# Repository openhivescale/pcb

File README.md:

PCB schemas and boards, eagle format (7.5)

mainboard is... the main board, with MCU including wifi, power, motor driver etc...

On this mainboard can be plugged ONE of the shield : 

- SFM10R1 : sifgox (Europe)
- RN2483A : LoraWan
- SIM800L : GSM 2G
- SIM7000E : GSM 4G Nb-IoT

- template : base for a future new shield

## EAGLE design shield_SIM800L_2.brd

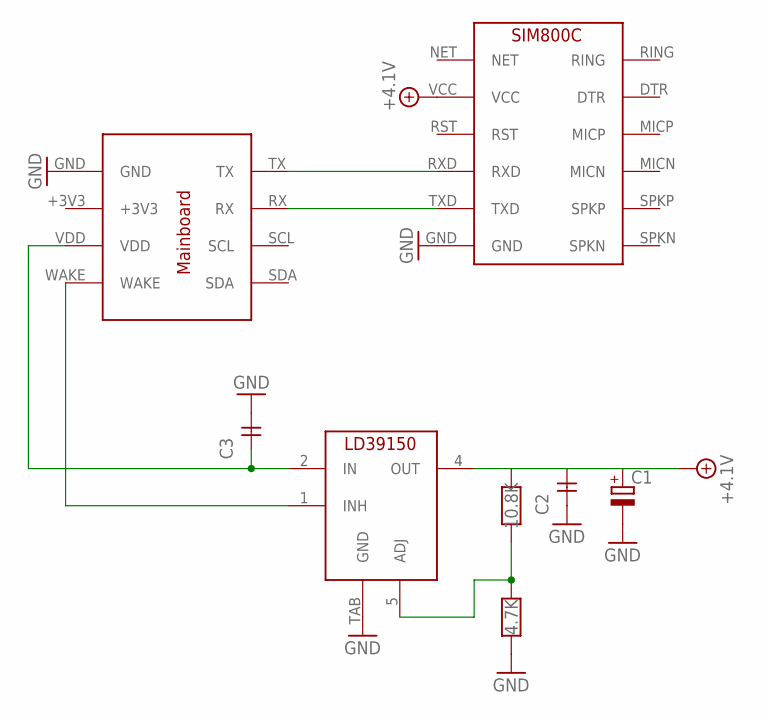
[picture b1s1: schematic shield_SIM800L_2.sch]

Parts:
C1: CPOL-EUE5-13; E5-13
C2, C3: CSMD_1206; SMD_RC_1206
R1: 10.8K; SMD_RC_1206
R2: 4.7K; SMD_RC_1206
U$1: SHIELD
U$2: LD39150PT-R; PPAK
U$6: SIM800L

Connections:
+3V3: U$1.+3V3
+4.1V: C1.+, C2.P$2 (2), R1.P$1, U$2.4 (OUT), U$6.VCC
GND: C1.-, C2.P$1 (1), C3.P$2 (2), R2.P$2, U$1.GND, U$2.TAB (GND), U$6.GND
unnamed: U$1.RX, U$6.TXD
unnamed: U$1.TX, U$6.RXD
unnamed: R1.P$2, R2.P$1, U$2.5 (ADJ)
unnamed: C3.P$1 (1), U$1.VDD, U$2.2 (IN)
unnamed: U$1.WAKE, U$2.1 (INH)

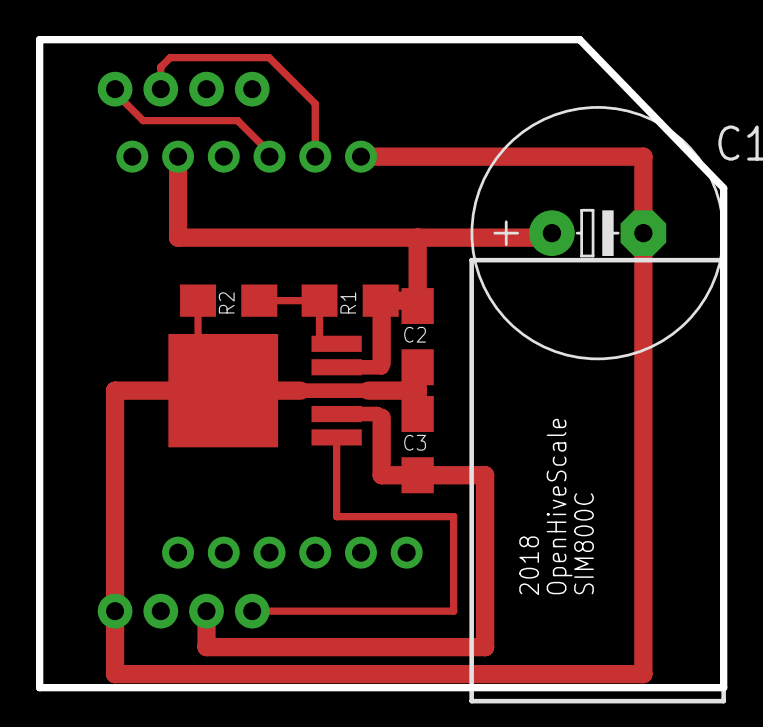
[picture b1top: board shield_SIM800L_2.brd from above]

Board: 2 copper layers, 38.0 x 36.0 mm, 8 parts (1 on the bottom side), 7 nets.

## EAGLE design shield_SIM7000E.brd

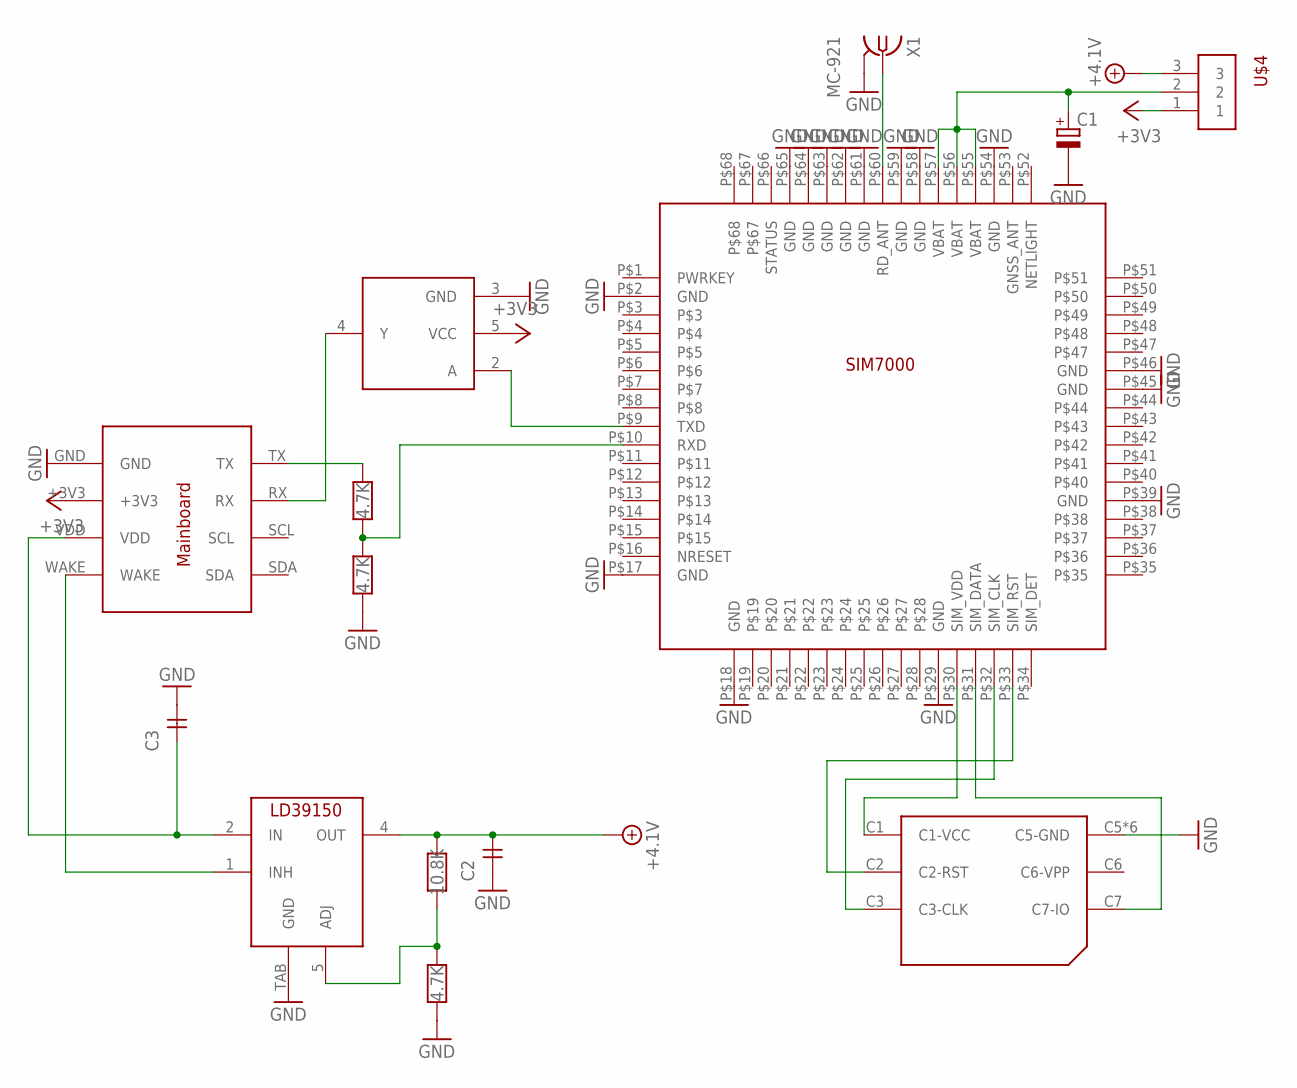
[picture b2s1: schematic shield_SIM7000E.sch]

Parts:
C1: CPOL-EUE5-13; E5-13
C2, C3: CSMD_1206; SMD_RC_1206
R1: 10.8K; SMD_RC_1206
R2, R3, R4: 4.7K; SMD_RC_1206
U$1: SHIELD
U$2: LD39150PT-R; PPAK
U$3: SIM7000
U$4: HEADER_1X3
U$5: SN75LV1T34; SOT23-5L-SIMPLE
U$6: SIM_SCYT
X1: MC-921

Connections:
+3V3: U$1.+3V3, U$4.1, U$5.5 (VCC)
+4.1V: C2.P$2 (2), R1.P$1, U$2.4 (OUT), U$4.3
GND: C1.-, C2.P$1 (1), C3.P$2 (2), R2.P$2, R4.P$1, U$1.GND, U$2.TAB (GND), U$3.P$2 (GND), U$3.P$17 (GND), U$3.P$18 (GND), U$3.P$29 (GND), U$3.P$39 (GND), U$3.P$45 (GND), U$3.P$46 (GND), U$3.P$54 (GND), U$3.P$58 (GND), U$3.P$59 (GND), U$3.P$61 (GND), U$3.P$62 (GND), U$3.P$63 (GND), U$3.P$64 (GND), U$3.P$65 (GND), U$5.3 (GND), U$6.C5 (C5-GND), U$6.GND@1 (C5-GND), U$6.GND@2 (C5-GND), U$6.GND@3 (C5-GND), U$6.GND@4 (C5-GND), U$6.GND@5 (C5-GND), X1.2@1 (GND), X1.2@2 (GND)
unnamed: R3.P$2, U$1.TX
unnamed: C1.+, U$3.P$55 (VBAT), U$3.P$56 (VBAT), U$3.P$57 (VBAT), U$4.2
unnamed: R1.P$2, R2.P$1, U$2.5 (ADJ)
unnamed: C3.P$1 (1), U$1.VDD, U$2.2 (IN)
unnamed: U$1.WAKE, U$2.1 (INH)
unnamed: U$3.P$9 (TXD), U$5.2 (A)
unnamed: R3.P$1, R4.P$2, U$3.P$10 (RXD)
unnamed: U$1.RX, U$5.4 (Y)
unnamed: U$3.P$30 (SIM_VDD), U$6.C1 (C1-VCC)
unnamed: U$3.P$31 (SIM_DATA), U$6.C7 (C7-IO)
unnamed: U$3.P$32 (SIM_CLK), U$6.C3 (C3-CLK)
unnamed: U$3.P$33 (SIM_RST), U$6.C2 (C2-RST)
unnamed: U$3.P$60 (RD_ANT), X1.1

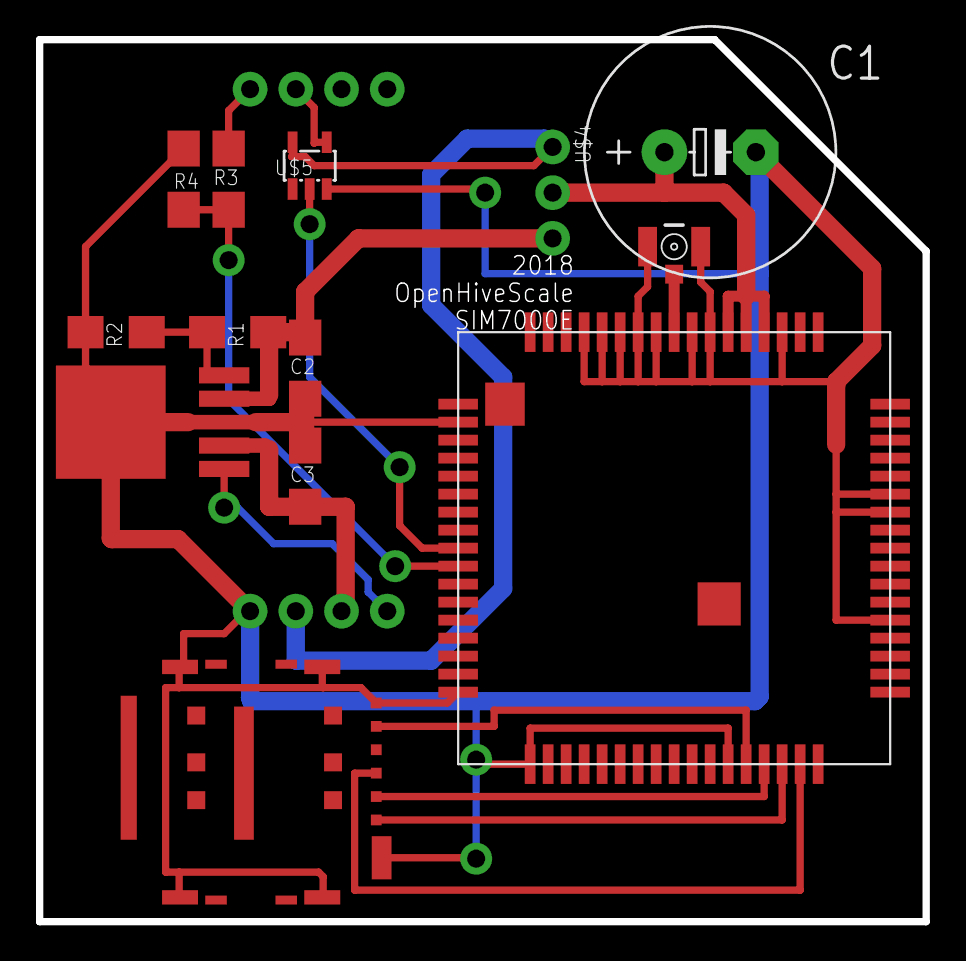
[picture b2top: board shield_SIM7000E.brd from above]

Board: 2 copper layers, 49.2 x 49.0 mm, 14 parts (0 on the bottom side), 16 nets.

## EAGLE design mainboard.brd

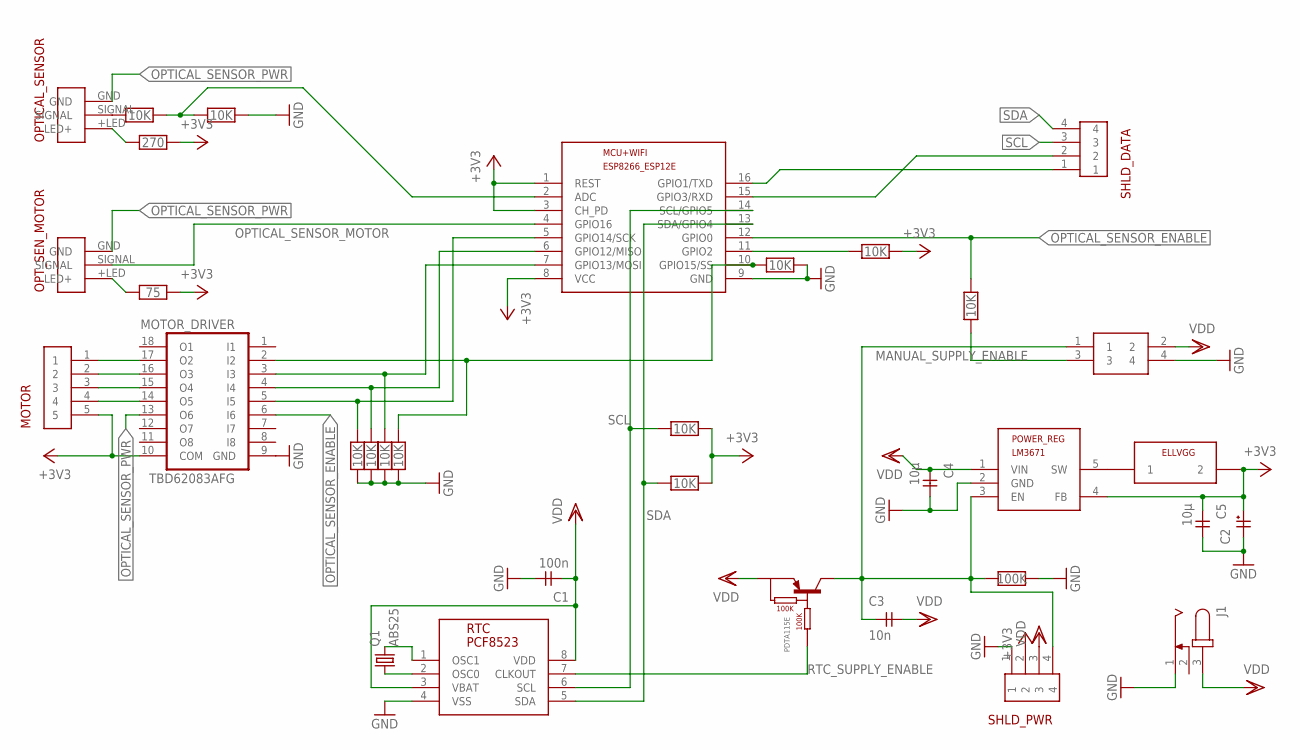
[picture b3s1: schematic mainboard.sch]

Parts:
C1: 100n; SMD_RC_1206
C2: C_POLSMD_M6.3; C_M6.3
C3: 10n; SMD_RC_1206
C4, C5: 10µ; SMD_RC_1206
DIL_SWITCH: HEADER_2X2
J1: JACK-PLUG0; SPC4077
L1: ELLVGG
MCU+WIFI: ESP8266-12EESP8266-ESP12E; ESP8266-ESP12E
MOTOR: B5B-XH-A
MOTOR_DRIVER: TBD62083AFG; SO18
OPTICAL_SENSOR: ENDSTOP
OPT_SEN_MOTOR: ENDSTOP
POWER_REG: LM3671NO_EXTRA_PAD; SOT23-5L-SIMPLE
Q1: ABS25
R1: 270; SMD_RC_1206
R2, R3, R5, R6, R7, R8, R9, R10, R11, R12, R13: 10K; SMD_RC_1206
R4: 100K; SMD_RC_1206
R14: 75; SMD_RC_1206
RTC: PCF8523TS; SO8
SHLD_DATA: HEADER_1X4
SHLD_PWR: HEADER_1X4
T1: PDTA115ET; SOT23

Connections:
+3V3: C2.+, C5.P$1 (1), L1.P$2 (2), MCU+WIFI.1 (REST), MCU+WIFI.3 (CH_PD), MCU+WIFI.8 (VCC), MOTOR.5, MOTOR_DRIVER.10 (COM), POWER_REG.4 (FB), R1.P$2, R9.P$2, R10.P$2, R11.P$2, R14.P$2, SHLD_PWR.2
GND: C1.P$2 (2), C2.GND, C4.P$2 (2), C5.P$2 (2), DIL_SWITCH.4, J1.1, MCU+WIFI.9 (GND), MOTOR_DRIVER.9 (GND), POWER_REG.2 (GND), R3.P$2, R4.P$1, R5.P$1, R6.P$1, R7.P$2, R12.P$1, R13.P$1, RTC.4 (VSS), SHLD_PWR.1
MANUAL_SUPPLY_ENABLE: C3.P$1 (1), DIL_SWITCH.1, POWER_REG.3 (EN), R4.P$2, SHLD_PWR.4, T1.3 (C)
unnamed: MOTOR.1, MOTOR_DRIVER.17 (O2)
unnamed: Q1.4 (2), RTC.1 (OSC1)
unnamed: L1.P$1 (1), POWER_REG.5 (SW)
unnamed: MOTOR.2, MOTOR_DRIVER.16 (O3)
unnamed: MCU+WIFI.7 (GPIO13/MOSI), MOTOR_DRIVER.3 (I3), R12.P$2
unnamed: MCU+WIFI.6 (GPIO12/MISO), MOTOR_DRIVER.4 (I4), R6.P$2
unnamed: MOTOR.3, MOTOR_DRIVER.15 (O4)
unnamed: MOTOR.4, MOTOR_DRIVER.14 (O5)
unnamed: OPT_SEN_MOTOR.+LED (LED+), R14.P$1
unnamed: MCU+WIFI.11 (GPIO2), R11.P$1
unnamed: MCU+WIFI.16 (GPIO1/TXD), SHLD_DATA.1
unnamed: MCU+WIFI.15 (GPIO3/RXD), SHLD_DATA.2
unnamed: MCU+WIFI.5 (GPIO14/SCK), MOTOR_DRIVER.5 (I5), R5.P$2
unnamed: MCU+WIFI.10 (GPIO15/SS), MOTOR_DRIVER.2 (I2), R7.P$1, R13.P$2
unnamed: MCU+WIFI.2 (ADC), R2.P$2, R3.P$1
unnamed: DIL_SWITCH.3, R8.P$2
unnamed: OPTICAL_SENSOR.SIGNAL, R2.P$1
unnamed: OPTICAL_SENSOR.+LED (LED+), R1.P$1
OPTICAL_SENSOR_ENABLE: MCU+WIFI.12 (GPIO0), MOTOR_DRIVER.6 (I6), R8.P$1
OPTICAL_SENSOR_MOTOR: MCU+WIFI.4 (GPIO16), OPT_SEN_MOTOR.SIGNAL
OPTICAL_SENSOR_PWR: MOTOR_DRIVER.13 (O6), OPTICAL_SENSOR.GND, OPT_SEN_MOTOR.GND
RTC_OSC: Q1.1, RTC.2 (OSC0)
RTC_SUPPLY_ENABLE: RTC.7 (CLKOUT), T1.1 (B)
SCL: MCU+WIFI.14 (SCL/GPIO5), R9.P$1, RTC.6 (SCL), SHLD_DATA.3
SDA: MCU+WIFI.13 (SDA/GPIO4), R10.P$1, RTC.5 (SDA), SHLD_DATA.4
VDD: C1.P$1 (1), C3.P$2 (2), C4.P$1 (1), DIL_SWITCH.2, J1.3, POWER_REG.1 (VIN), RTC.3 (VBAT), RTC.8 (VDD), SHLD_PWR.3, T1.2 (E)

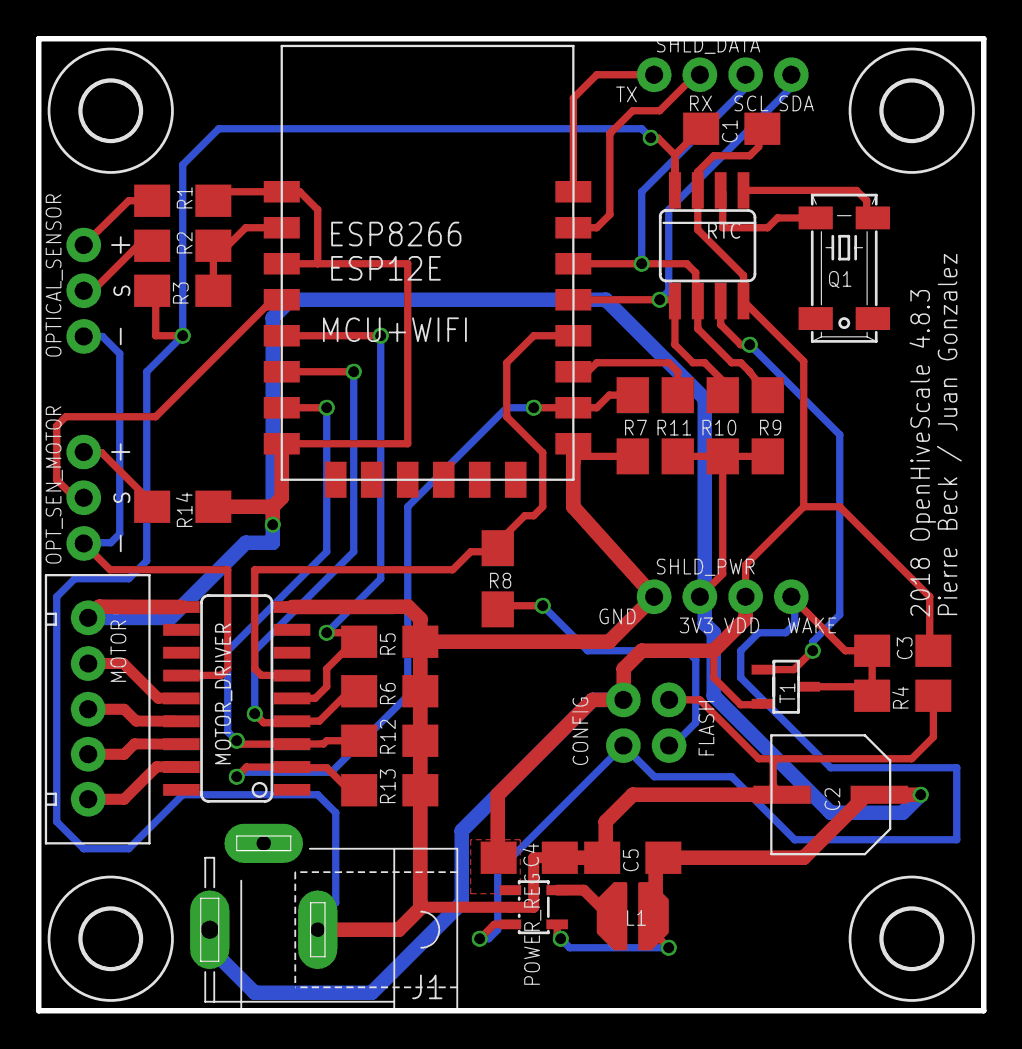
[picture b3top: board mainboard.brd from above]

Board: 2 copper layers, 52.5 x 54.0 mm, 37 parts (0 on the bottom side), 29 nets.

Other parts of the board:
U$2, U$3, U$4, U$5: 3,2

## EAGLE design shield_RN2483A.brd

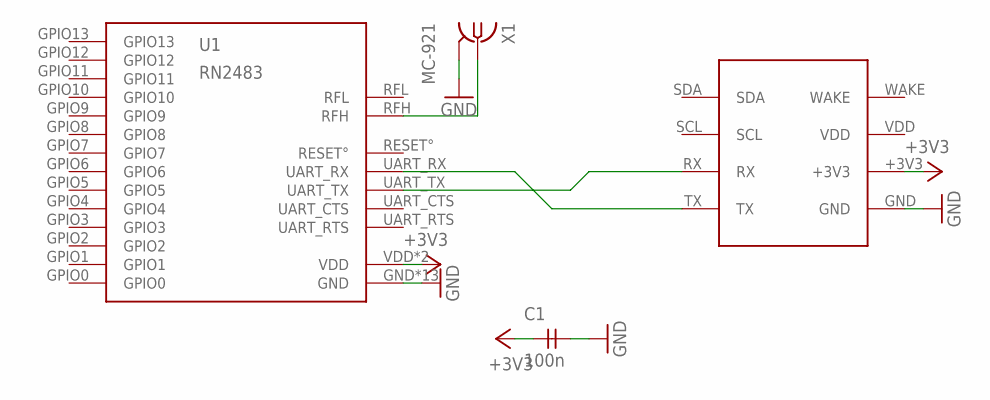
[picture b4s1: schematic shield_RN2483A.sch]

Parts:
C1: 100n; SMD_RC_1206
U1: RN2483
U$1: SHIELD
X1: MC-921

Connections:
+3V3: C1.P$1 (1), U1.VDD, U1.VDD2 (VDD), U$1.+3V3
GND: C1.P$2 (2), U1.GND, U1.GND1 (GND), U1.GND2 (GND), U1.GND3 (GND), U1.GND4 (GND), U1.GND5 (GND), U1.GND6 (GND), U1.GND7 (GND), U1.GND8 (GND), U1.GND9 (GND), U1.GND10 (GND), U1.GND11 (GND), U1.GND12 (GND), U$1.GND, X1.2@1 (GND), X1.2@2 (GND)
unnamed: U1.UART_TX, U$1.RX
unnamed: U1.UART_RX, U$1.TX
unnamed: U1.RFH, X1.1
VDD: U$1.VDD

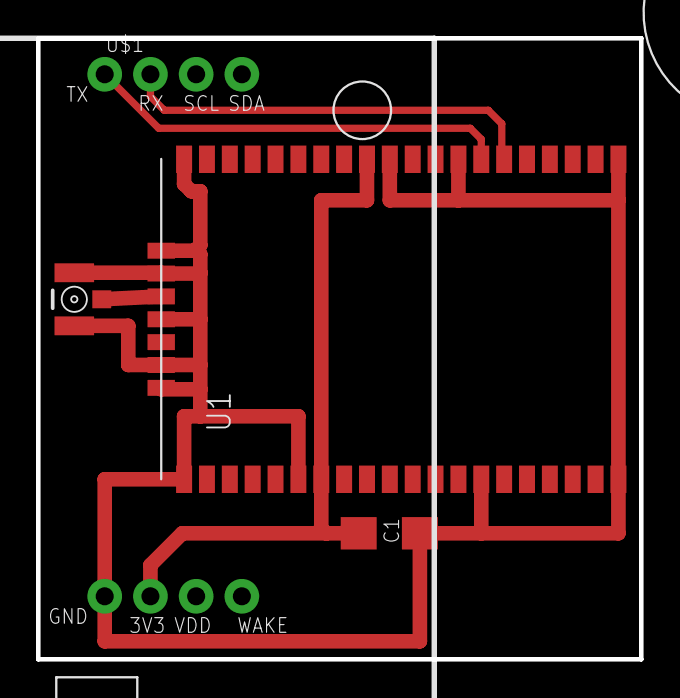
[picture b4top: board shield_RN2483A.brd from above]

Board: 2 copper layers, 33.5 x 34.5 mm, 4 parts (0 on the bottom side), 5 nets.

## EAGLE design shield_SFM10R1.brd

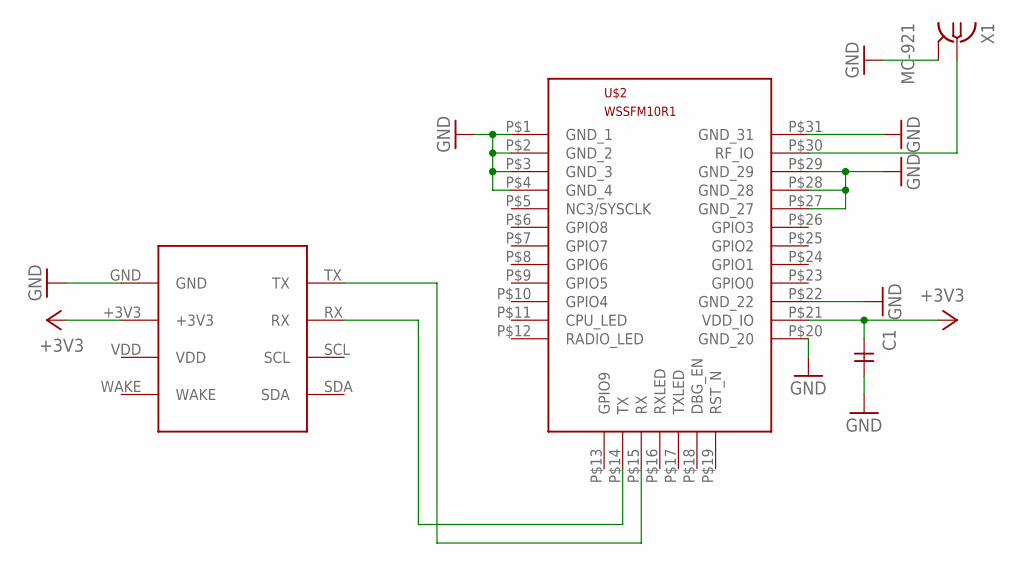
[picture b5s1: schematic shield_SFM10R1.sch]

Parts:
C1: CSMD_1206; SMD_RC_1206
U$1: SHIELD
U$2: SFM10R1
X1: MC-921

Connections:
+3V3: C1.P$1 (1), U$1.+3V3, U$2.P$21 (VDD_IO)
GND: C1.P$2 (2), U$1.GND, U$2.P$1 (GND_1), U$2.P$2 (GND_2), U$2.P$3 (GND_3), U$2.P$4 (GND_4), U$2.P$20 (GND_20), U$2.P$22 (GND_22), U$2.P$27 (GND_27), U$2.P$28 (GND_28), U$2.P$29 (GND_29), U$2.P$31 (GND_31), X1.2@1 (GND), X1.2@2 (GND)
unnamed: U$1.TX, U$2.P$15 (RX)
unnamed: U$1.RX, U$2.P$14 (TX)
unnamed: U$2.P$30 (RF_IO), X1.1
VDD: U$1.VDD

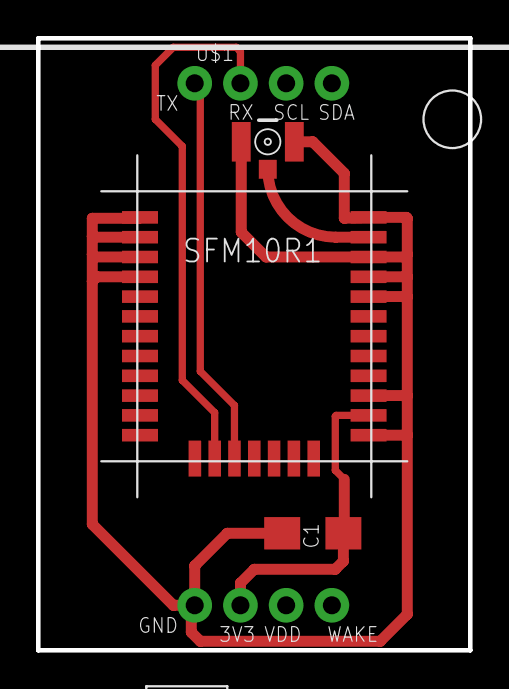
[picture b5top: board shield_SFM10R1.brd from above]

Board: 2 copper layers, 24.0 x 34.0 mm, 4 parts (0 on the bottom side), 5 nets.

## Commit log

2018-10-04 schema en png
2018-10-04 SIM800 v2 + SIM7000
2018-10-04 schema mainboard en png
2018-10-04 removed v1 of SIM800L, that doesn't work reliably
